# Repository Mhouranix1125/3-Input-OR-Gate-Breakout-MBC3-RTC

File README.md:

# 3-Input-OR-Gate-Breakout-MBC3-RTC
Utilizes the 74LVC1G332GV,125 OR Gate IC Pinout on a neat board, and allows one to utilize the pinouts.

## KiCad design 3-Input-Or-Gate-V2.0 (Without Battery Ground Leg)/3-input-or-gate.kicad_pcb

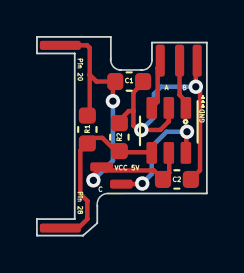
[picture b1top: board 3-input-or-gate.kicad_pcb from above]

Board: 2 copper layers, 9.4 x 11.0 mm, 5 parts (0 on the bottom side), 3 nets.

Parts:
C1: 0.01uf (maybe 100uf); C_0603_1608Metric
C2: 0.1uf; C_0603_1608Metric
R1: C_0603_1608Metric
R2: 0.01uf; C_0603_1608Metric
U5: 74LVC1G332GW,125; TSOP-6_1.65x3.05mm_P0.95mm

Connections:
CE: R1.3, R2.6, U5.4
GND: C1.6, C2.7, R2.5, U5.2
VCC5V: C1.5, C2.8, R1.2, U5.5

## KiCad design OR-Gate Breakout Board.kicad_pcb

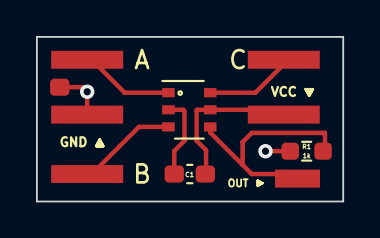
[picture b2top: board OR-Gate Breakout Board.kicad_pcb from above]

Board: 2 copper layers, 17.0 x 9.1 mm, 3 parts (0 on the bottom side), 3 nets.

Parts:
1k: 1k; R_0603_1608Metric_Pad0.98x0.95mm_HandSolder
C1: C_0603_1608Metric_Pad1.08x0.95mm_HandSolder
U5: 74LVC1G332GW,125; TSOP-6_1.65x3.05mm_P0.95mm

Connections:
GND: 1k.7, C1.1, U5.2
OUT: 1k.8, U5.4
VCC: C1.2, U5.5

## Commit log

2022-10-19 Working KICAD File. Completed.
2022-10-19 adding gerbers
2022-11-05 Updated design to be a little more usable. Still need to consider resistors and stuff. Do not use this version. WIP
2022-11-07 Alpha Prototype for OR Gate Breakout.
2022-11-07 Replacing
2022-11-07 Adding gerbers and such
2022-11-07 Added some different options for a less busy looking main PCB
2022-11-07 Updated files to
2022-11-07 Changed footprint of or gate to be more in line with the IC
